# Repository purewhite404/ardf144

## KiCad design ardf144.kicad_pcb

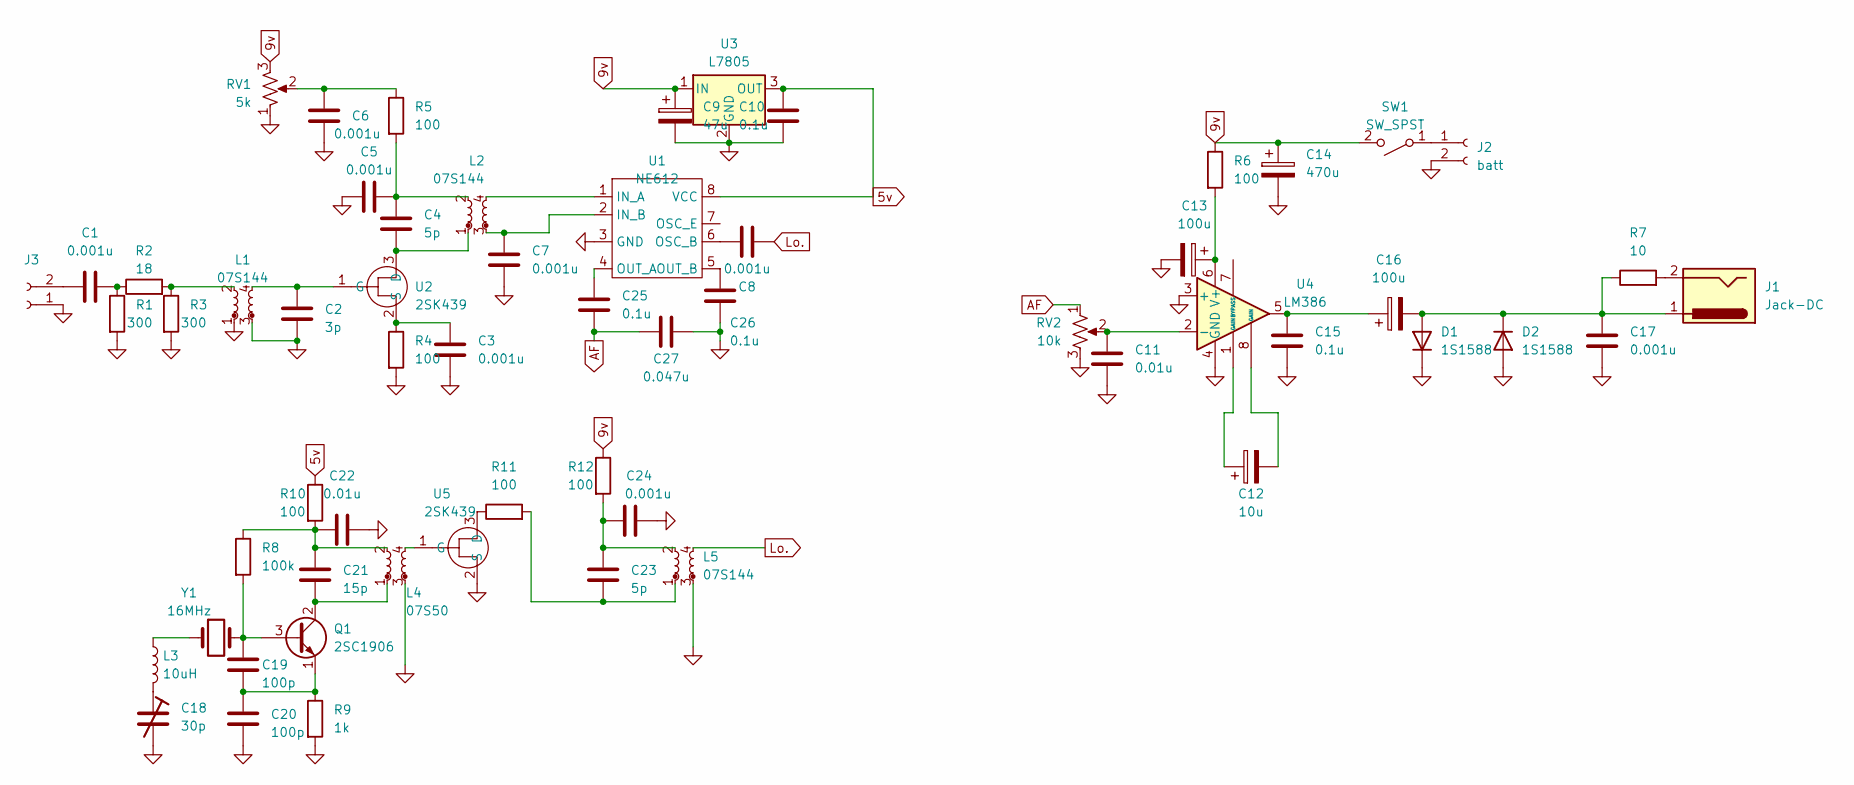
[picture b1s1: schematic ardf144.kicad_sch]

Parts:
C1, C3, C5, C6, C7, C8, C17, C24: 0.001u; C_Disc_D5.0mm_W2.5mm_P2.50mm
C2: 3p; C_Disc_D5.0mm_W2.5mm_P2.50mm
C4, C23: 5p; C_Disc_D5.0mm_W2.5mm_P2.50mm
C9: 47u; CP_Radial_D6.3mm_P2.50mm
C10, C15, C25: 0.1u; C_Disc_D5.0mm_W2.5mm_P2.50mm
C11, C22: 0.01u; C_Disc_D5.0mm_W2.5mm_P2.50mm
C12: 10u; CP_Radial_D6.3mm_P2.50mm
C13, C16: 100u; CP_Radial_D6.3mm_P2.50mm
C14: 470u; CP_Radial_D6.3mm_P2.50mm
C18: 30p; c_trim
C19, C20: 100p; C_Disc_D5.0mm_W2.5mm_P2.50mm
C21: 15p; C_Disc_D5.0mm_W2.5mm_P2.50mm
C26: 0.1u; C_Disc_D5.0mm_W2.5mm_P5.00mm
C27: 0.047u; C_Disc_D5.0mm_W2.5mm_P2.50mm
D1: 1S1588; D_DO-41_SOD81_P10.16mm_Horizontal
D2: 1S1588; D_DO-41_SOD81_P2.54mm_Vertical_AnodeUp
J1: Jack-DC; 2.5jack
J2: batt; PinSocket_1x02_P2.54mm_Vertical
J3: ant; PinSocket_1x02_P2.54mm_Vertical
L1, L2, L5: 07S144; FCZ
L3: 10uH; L_Axial_L5.3mm_D2.2mm_P7.62mm_Horizontal_Vishay_IM-1
L4: 07S50; FCZ
Q1: 2SC1906; TO-92_Inline_Wide
R1, R3: 300; R_Axial_DIN0207_L6.3mm_D2.5mm_P7.62mm_Horizontal
R2: 18; R_Axial_DIN0207_L6.3mm_D2.5mm_P7.62mm_Horizontal
R4, R5, R6, R10, R11, R12: 100; R_Axial_DIN0207_L6.3mm_D2.5mm_P7.62mm_Horizontal
R7: 10; R_Axial_DIN0207_L6.3mm_D2.5mm_P7.62mm_Horizontal
R8: 100k; R_Axial_DIN0207_L6.3mm_D2.5mm_P7.62mm_Horizontal
R9: 1k; R_Axial_DIN0207_L6.3mm_D2.5mm_P7.62mm_Horizontal
RV1: 5k; Potentiometer_Alps_RK09Y11_Single_Horizontal
RV2: 10k; Potentiometer_Vishay_T73YP_Vertical
SW1: SW_SPST; SW_CuK_JS202011CQN_DPDT_Straight
U1: NE612; DIP-8_W7.62mm
U2, U5: 2SK439; TO-92_Inline_Wide
U3: L7805; TO-220-3_Vertical
U4: LM386; DIP-8_W7.62mm
Y1: 16MHz; Crystal_HC49-4H_Vertical

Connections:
5v: C10.1, R10.1, U1.8 (VCC), U3.3 (OUT)
9v: C9.1, C14.1, R6.1, R12.1, RV1.3, SW1.2 (B), U3.1 (IN)
AF: C25.2, C27.1, RV2.1
GND: C2.2, C3.2, C5.1, C6.2, C7.2, C9.2, C10.2, C11.2, C13.2, C14.2, C15.2, C17.2, C18.2, C20.2, C22.2, C24.2, C26.2, C27.2, D1.1 (K), D2.2 (A), J2.2, J3.1, L1.1, L1.3, L4.3, L5.3, R1.2, R3.2, R4.2, R9.2, RV1.1, RV2.3, U1.3 (GND), U3.2 (GND), U4.3 (+), U4.4 (GND), U5.2 (S)
Lo.: C8.2, L5.4
unnamed: C1.2, R1.1, R2.1
unnamed: C4.1, C5.2, L2.2, R5.2
unnamed: C6.1, R5.1, RV1.2
unnamed: C12.1, U4.1 (GAIN)
unnamed: C12.2, U4.8 (GAIN)
unnamed: C15.1, C16.1, U4.5
unnamed: C18.1, L3.2
unnamed: C21.1, C22.1, L4.2, R8.1, R10.2
unnamed: C23.1, C24.1, L5.2, R12.2
unnamed: C23.2, L5.1, R11.2
unnamed: C16.2, C17.1, D1.2 (A), D2.1 (K), J1.1, R7.1
unnamed: J1.2, R7.2
unnamed: J2.1, SW1.1 (A)
unnamed: C1.1, J3.2
unnamed: L1.2, R2.2, R3.1
unnamed: L3.1, Y1.1
unnamed: C19.1, Q1.3 (B), R8.2, Y1.2
unnamed: C21.2, L4.1, Q1.2 (C)
unnamed: C19.2, C20.1, Q1.1 (E), R9.1
unnamed: L2.4, U1.1 (IN_A)
unnamed: C7.1, L2.3, U1.2 (IN_B)
unnamed: C8.1, U1.6 (OSC_B)
unnamed: C25.1, U1.4 (OUT_A)
unnamed: C26.1, U1.5 (OUT_B)
unnamed: C4.2, L2.1, U2.3 (D)
unnamed: C2.1, L1.4, U2.1 (G)
unnamed: C3.1, R4.1, U2.2 (S)
unnamed: C11.1, RV2.2, U4.2 (-)
unnamed: C13.1, R6.2, U4.6 (V+)
unnamed: R11.1, U5.3 (D)
unnamed: L4.4, U5.1 (G)

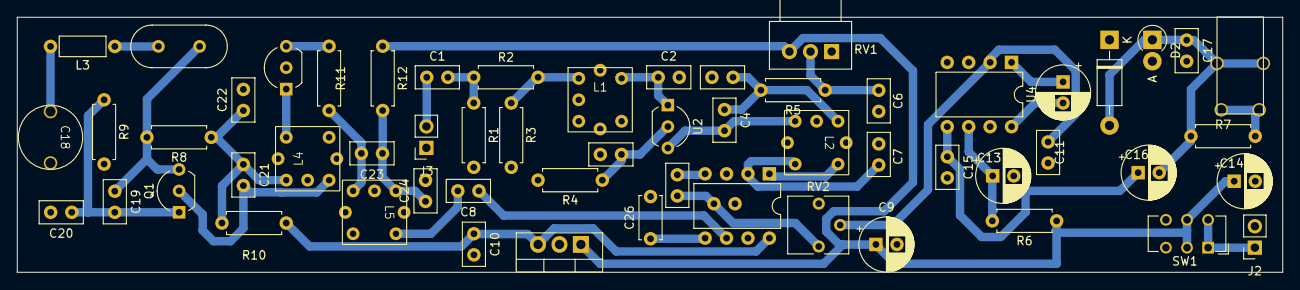
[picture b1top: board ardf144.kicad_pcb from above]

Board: 2 copper layers, 150.0 x 30.2 mm, 59 parts (1 on the bottom side), 36 nets.

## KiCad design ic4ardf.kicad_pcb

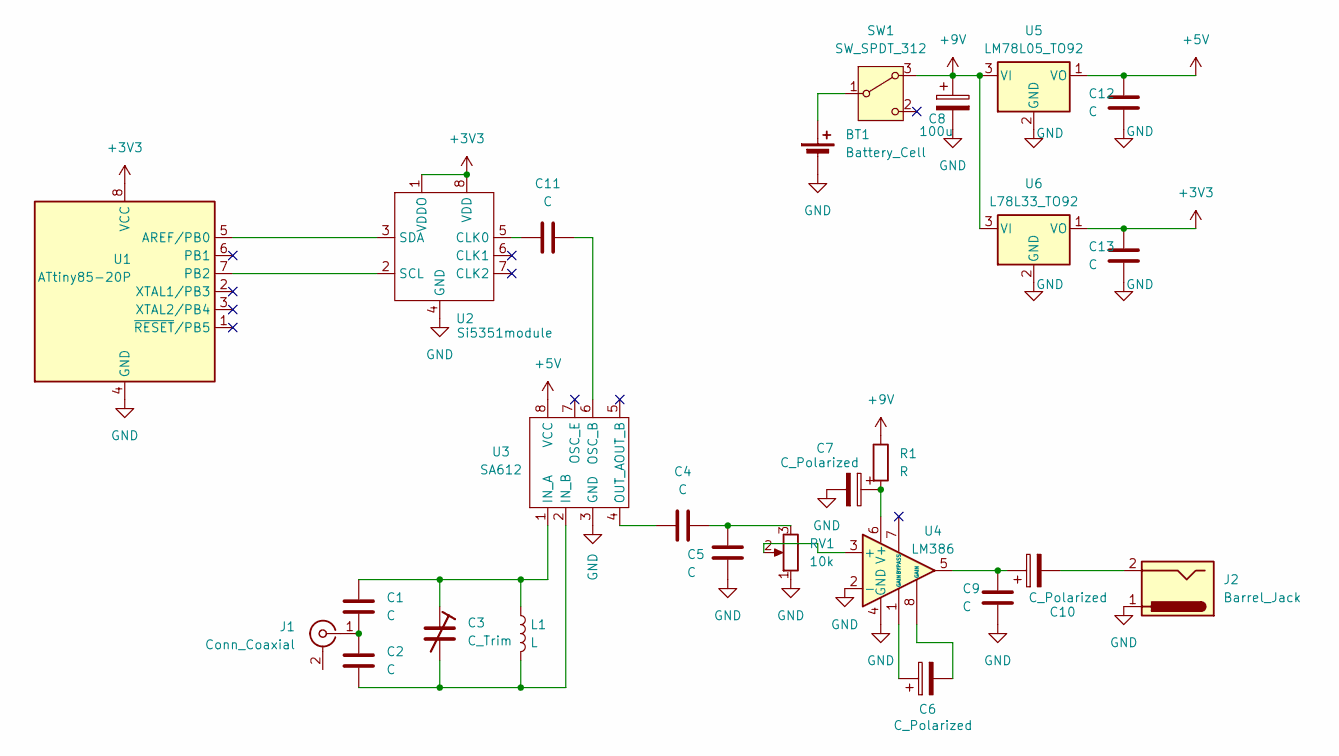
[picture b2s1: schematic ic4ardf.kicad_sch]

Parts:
BT1: Battery_Cell; PinHeader_1x02_P2.54mm_Vertical
C1, C2, C4, C5, C9, C11, C12, C13: C; C_Disc_D4.3mm_W1.9mm_P5.00mm
C3: C_Trim; c_trim
C6, C7, C10: C_Polarized; CP_Radial_D6.3mm_P2.50mm
C8: 100u; CP_Radial_D6.3mm_P2.50mm
J1: Conn_Coaxial; SMA_Amphenol_132289_EdgeMount
J2: Barrel_Jack; 2.5jack
L1: L; L_Axial_L5.3mm_D2.2mm_P2.54mm_Vertical_Vishay_IM-1
R1: R; R_Axial_DIN0207_L6.3mm_D2.5mm_P7.62mm_Horizontal
RV1: 10k; Potentiometer_Vishay_T73YP_Vertical
SW1: SW_SPDT_312; SW
U1: ATtiny85-20P; DIP-8_W7.62mm
U2: Si5351module; DIP-8_W7.62mm
U3: SA612; DIP-8_W7.62mm
U4: LM386; DIP-8_W7.62mm
U5: LM78L05_TO92; TO-92_Inline_Wide
U6: L78L33_TO92; TO-92_Inline_Wide

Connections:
+3V3: C13.1, U1.8 (VCC), U2.1 (VDDO), U2.8 (VDD), U6.1 (VO)
+5V: C12.1, U3.8 (VCC), U5.1 (VO)
+9V: C8.1, R1.1, SW1.3 (A), U5.3 (VI), U6.3 (VI)
GND: BT1.2 (-), C5.2, C7.2, C8.2, C9.2, C12.2, C13.2, J2.1, RV1.1, U1.4 (GND), U2.4 (GND), U3.3 (GND), U4.2 (-), U4.4 (GND), U5.2 (GND), U6.2 (GND)
unnamed: BT1.1 (+), SW1.1 (B)
unnamed: C4.2, C5.1, RV1.3
unnamed: C6.1, U4.1 (GAIN)
unnamed: C6.2, U4.8 (GAIN)
unnamed: C9.1, C10.1, U4.5
unnamed: C10.2, J2.2
unnamed: C1.2, C2.1, J1.1 (In)
unnamed: U1.5 (AREF/PB0), U2.3 (SDA)
unnamed: U1.7 (PB2), U2.2 (SCL)
unnamed: C11.1, U2.5 (CLK0)
unnamed: C1.1, C3.1, L1.1, U3.1 (IN_A)
unnamed: C2.2, C3.2, L1.2, U3.2 (IN_B)
unnamed: C11.2, U3.6 (OSC_B)
unnamed: C4.1, U3.4 (OUT_A)
unnamed: RV1.2, U4.3 (+)
unnamed: C7.1, R1.2, U4.6 (V+)

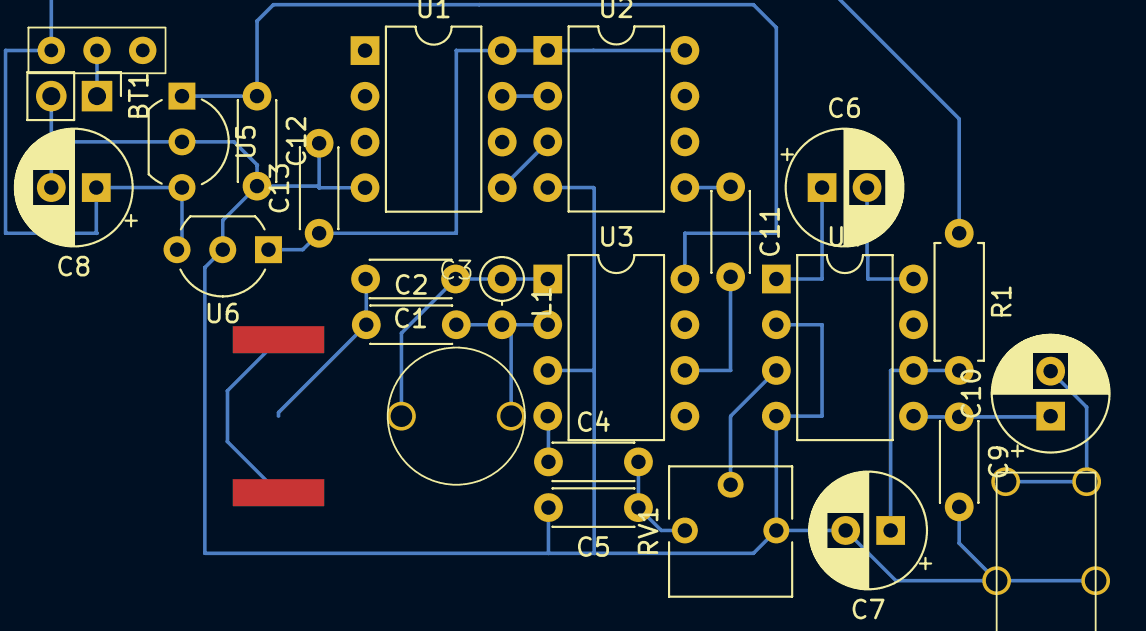
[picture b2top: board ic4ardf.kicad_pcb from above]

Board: 2 copper layers, 26 parts (1 on the bottom side), 20 nets.

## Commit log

2024-03-04 init
2024-03-05 second
2024-03-05 add gitignore
2024-03-05 fix gitignore
2024-03-09 fix 3
2024-03-12 fix capacitance
2024-04-03 add ic4
2024-04-05 fix attiny vcc +3v3 from +5v
